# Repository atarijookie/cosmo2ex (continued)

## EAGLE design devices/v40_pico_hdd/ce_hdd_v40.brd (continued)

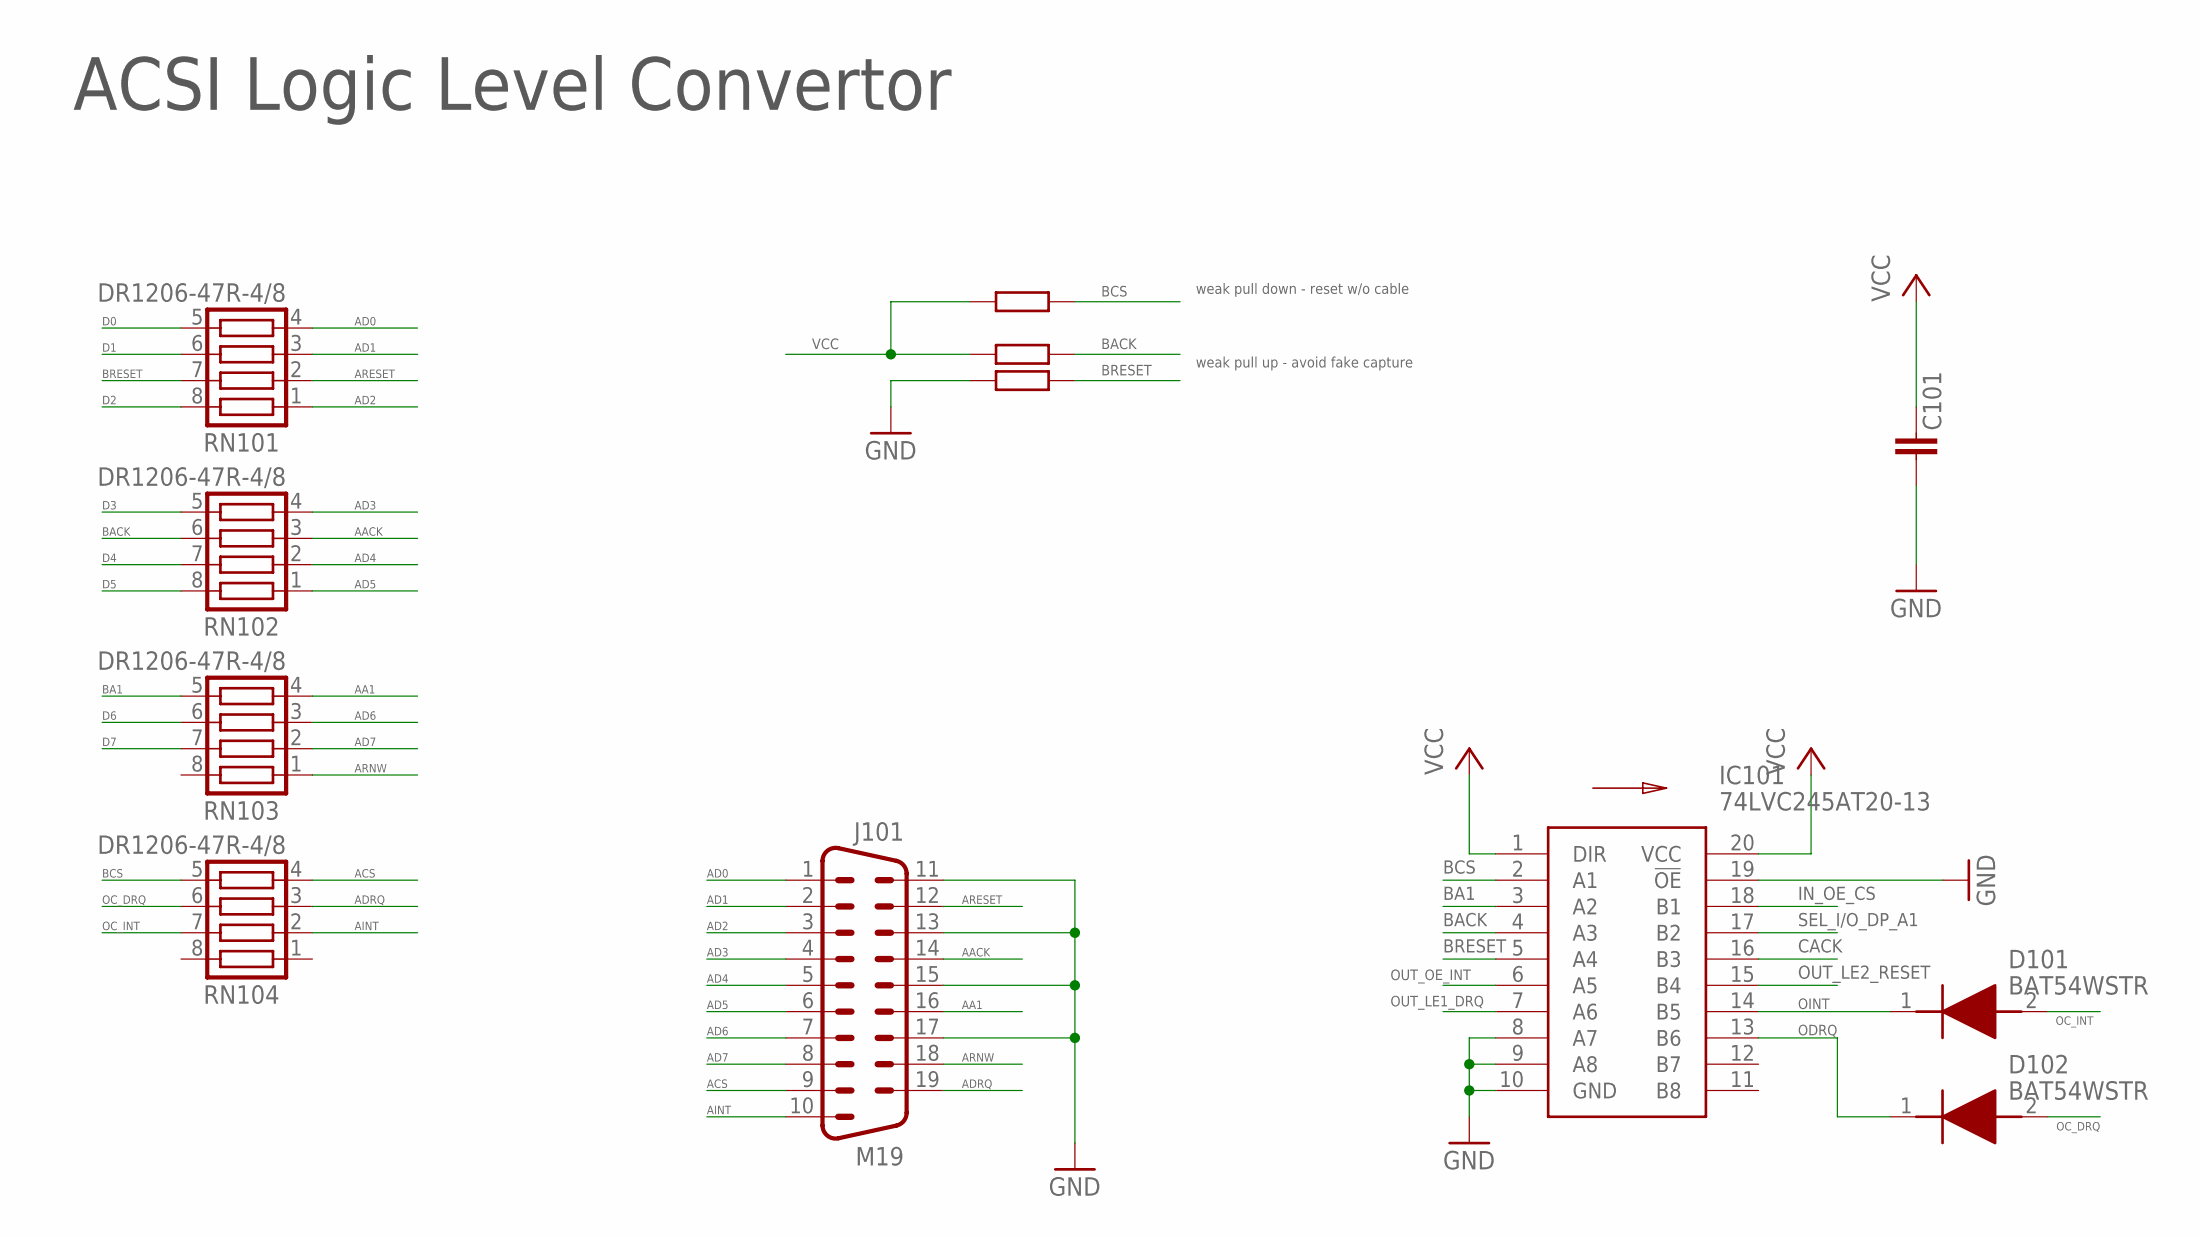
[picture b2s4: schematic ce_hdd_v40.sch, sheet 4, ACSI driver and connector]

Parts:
C101: 1 uF; C0603
D101: BAT54WSTR; SOD2613X100N
D102: BAT54WSTR; SOD2613X100N; MANUFACTURER_PART_NUMBER BAT54WSTR
IC101: 74LVC245AT20-13; SOP65P640X120-20N
J101: M19
R102, R103, R104: 10k; R0603
RN101, RN102, RN103, RN104: DR1206-47R-4/8; CTS742C083

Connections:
AA1: J101.16, RN103.4
AACK: J101.14, RN102.3
ACS: J101.9, RN104.4
AD0: J101.1, RN101.4
AD1: J101.2, RN101.3
AD2: J101.3, RN101.1
AD3: J101.4, RN102.4
AD4: J101.5, RN102.2
AD5: J101.6, RN102.1
AD6: J101.7, RN103.3
AD7: J101.8, RN103.2
ADRQ: J101.19, RN104.3
AINT: J101.10, RN104.2
ARESET: J101.12, RN101.2
ARNW: J101.18, RN103.1
BA1: IC101.3 (A2), RN103.5
BACK: IC101.4 (A3), R103.2, RN102.6
BCS: IC101.2 (A1), R102.2, RN104.5
BRESET: IC101.5 (A4), R104.2, RN101.7
CACK: IC101.16 (B3); also elsewhere on the board
D0: RN101.5; also elsewhere on the board
D1: RN101.6; also elsewhere on the board
D2: RN101.8; also elsewhere on the board
D3: RN102.5; also elsewhere on the board
D4: RN102.7; also elsewhere on the board
D5: RN102.8; also elsewhere on the board
D6: RN103.6; also elsewhere on the board
D7: RN103.7; also elsewhere on the board
GND: C101.2, IC101.8 (A7), IC101.9 (A8), IC101.10 (GND), IC101.19 (!OE), J101.11, J101.13, J101.15, J101.17, R104.1; also elsewhere on the board
IN_OE_CS: IC101.18 (B1); also elsewhere on the board
OC_DRQ: D102.2 (A), RN104.6
OC_INT: D101.2 (A), RN104.7
ODRQ: D102.1 (K), IC101.13 (B6)
OINT: D101.1 (K), IC101.14 (B5)
OUT_LE1_DRQ: IC101.7 (A6); also elsewhere on the board
OUT_LE2_RESET: IC101.15 (B4); also elsewhere on the board
OUT_OE_INT: IC101.6 (A5); also elsewhere on the board
SEL_I/O_DP_A1: IC101.17 (B2); also elsewhere on the board
VCC: C101.1, IC101.1 (DIR), IC101.20 (VCC), R102.1, R103.1; also elsewhere on the board

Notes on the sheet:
ACSI Logic Level Convertor
weak pull down - reset w/o cable
weak pull up - avoid fake capture

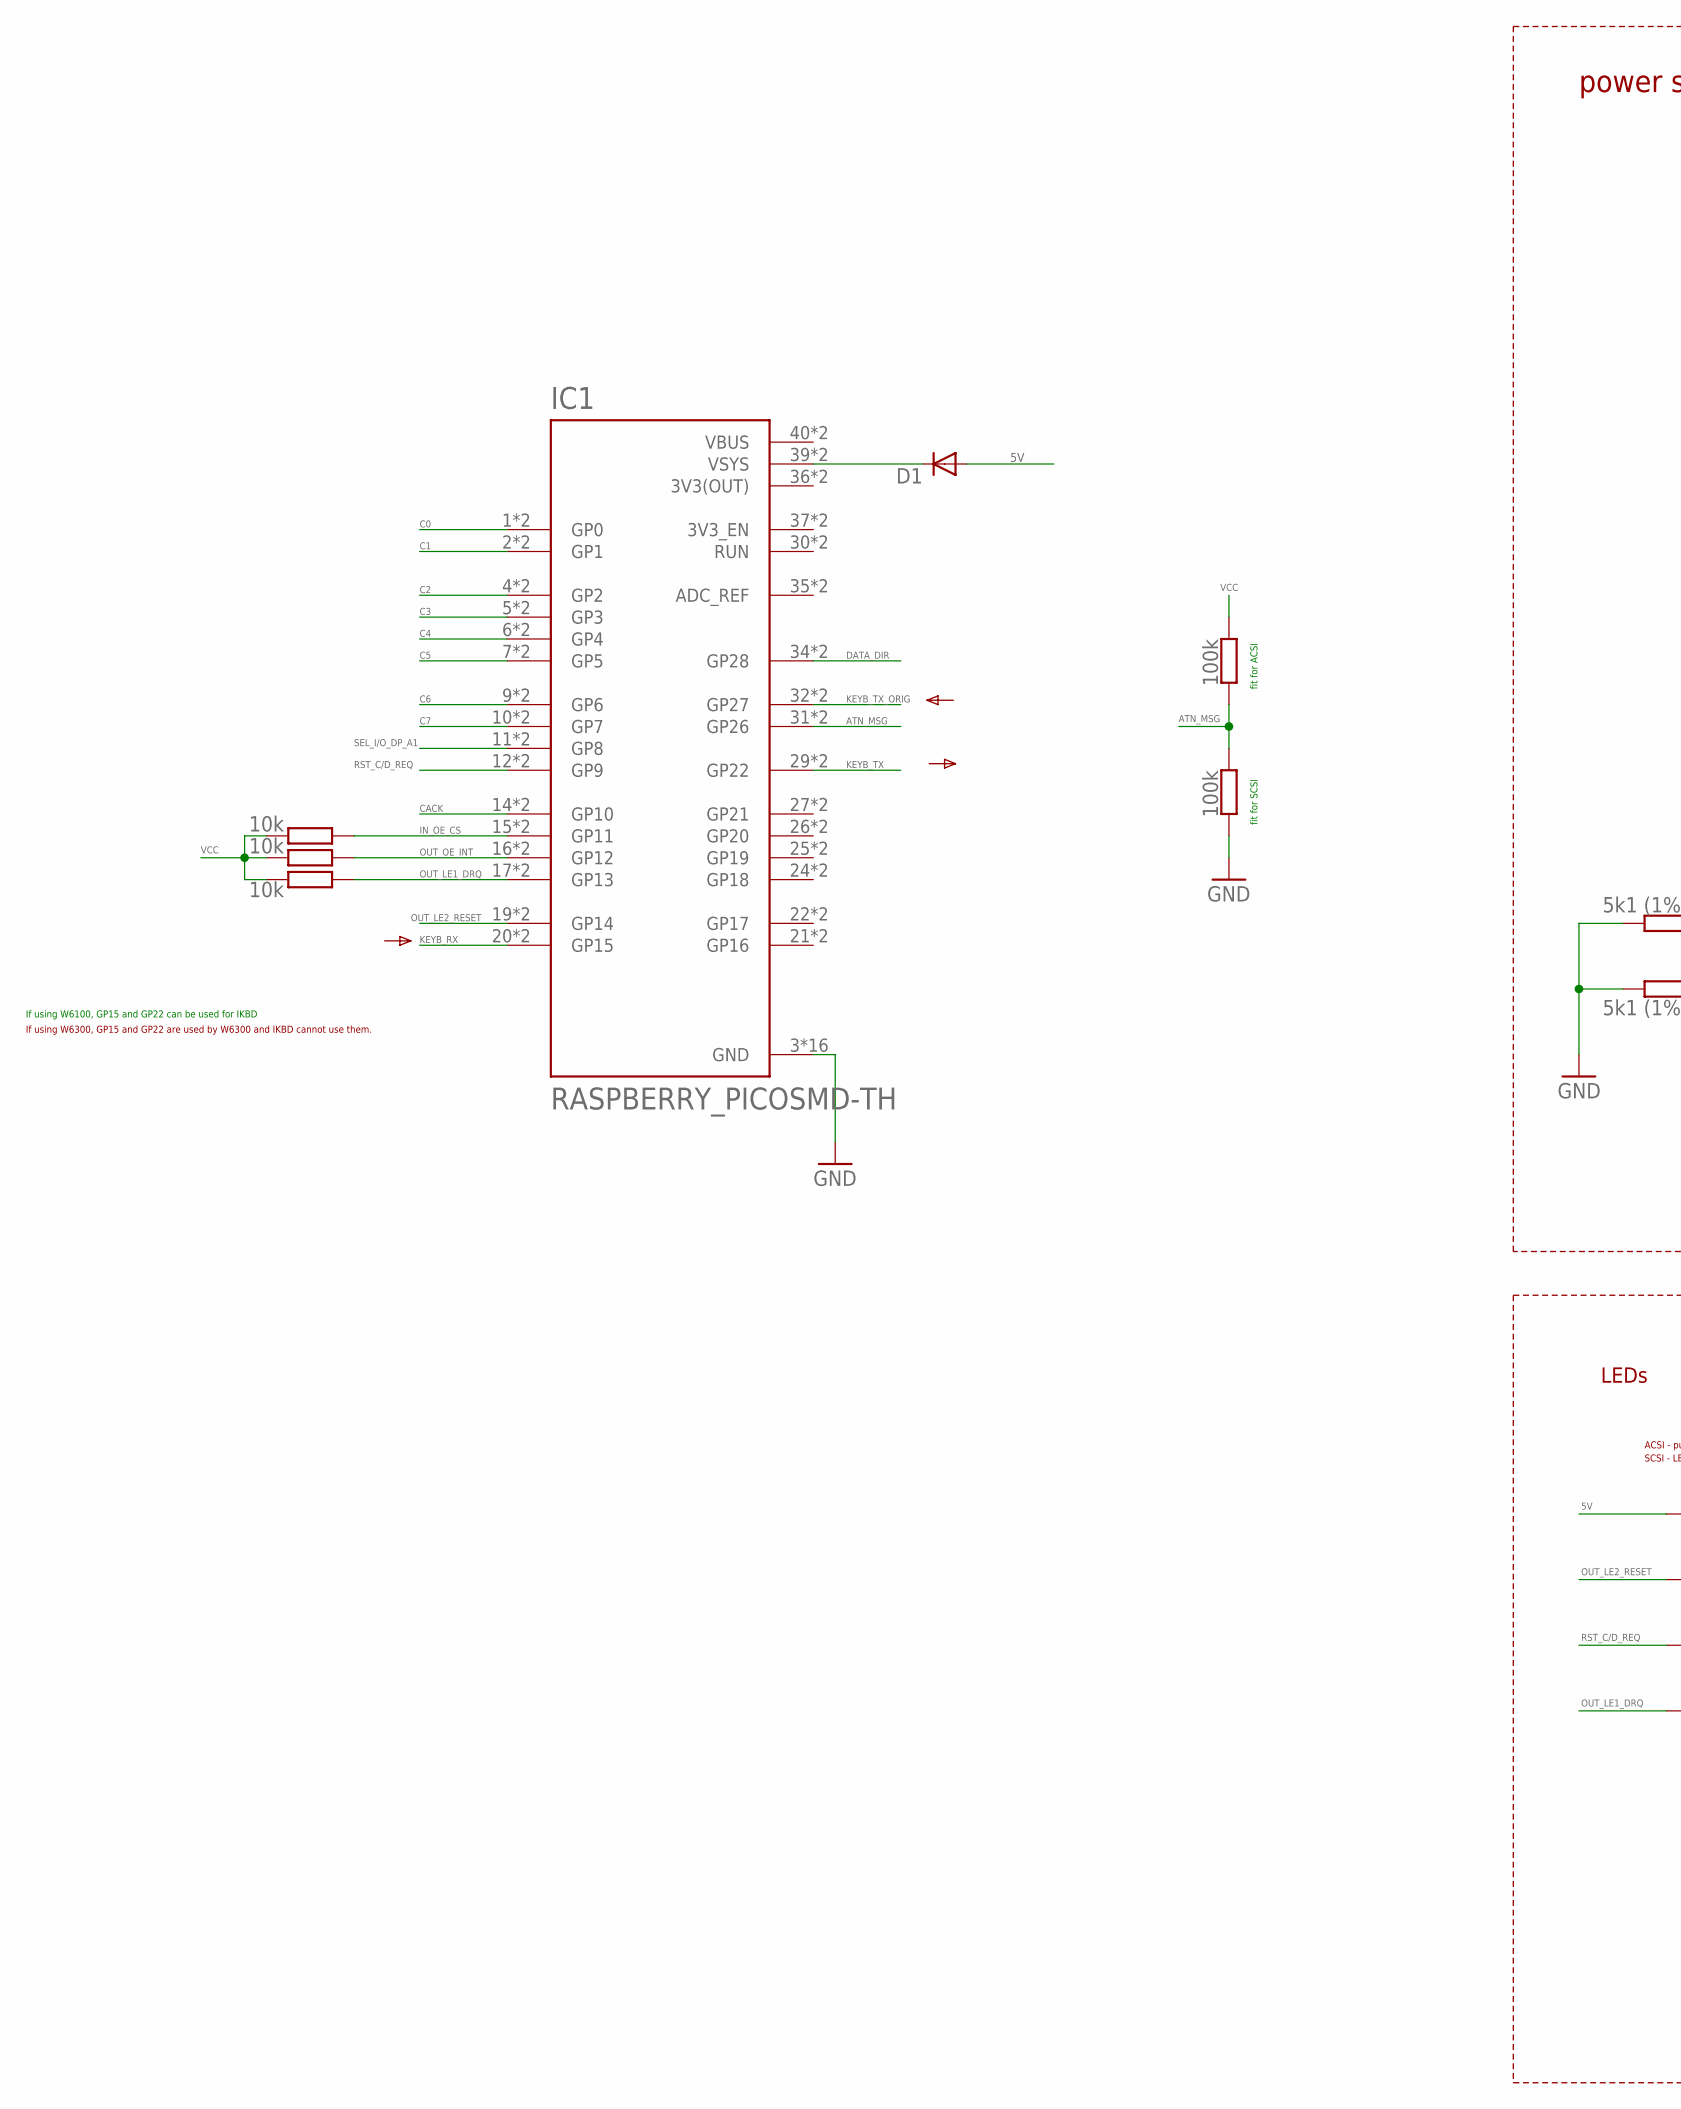
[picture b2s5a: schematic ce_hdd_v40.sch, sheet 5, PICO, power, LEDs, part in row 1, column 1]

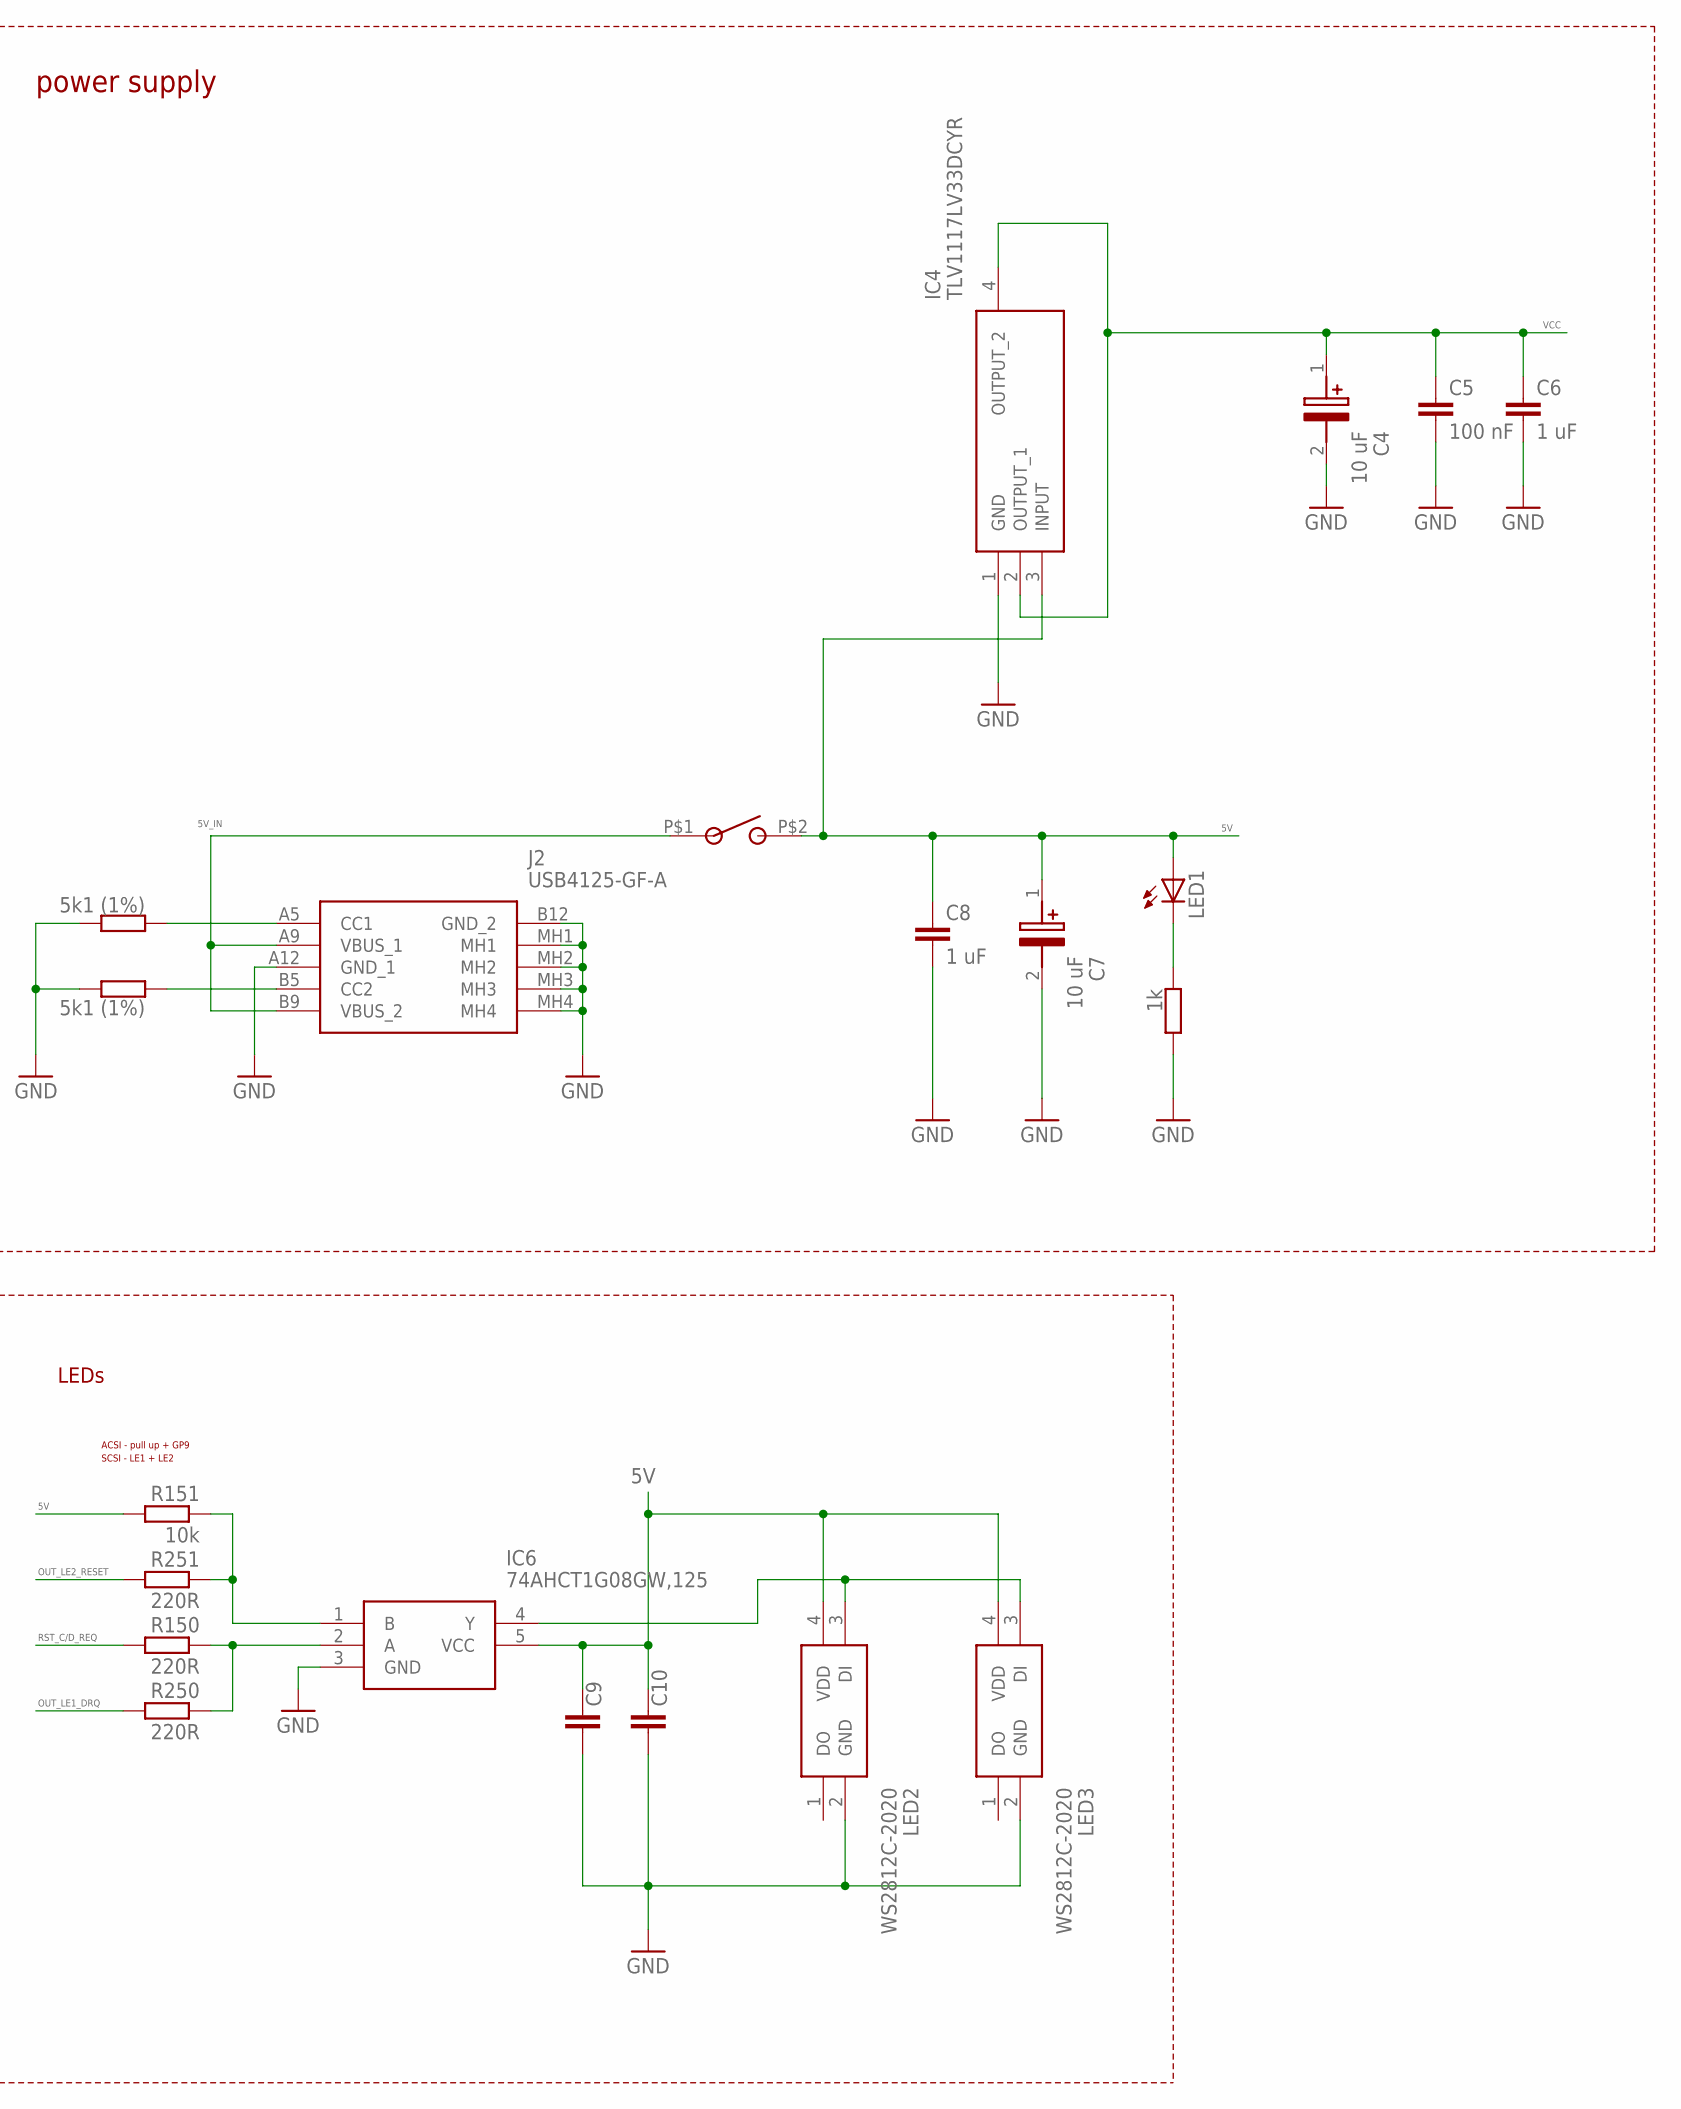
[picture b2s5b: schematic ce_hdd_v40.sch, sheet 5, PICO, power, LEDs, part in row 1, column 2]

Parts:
C4: 10 uF; CAPPM3528X210N; MANUFACTURER_PART_NUMBER 293D106X9016B2TE3
C5, C9, C10: 100 nF; C0603
C6, C8: 1 uF; C0603
C7: 10 uF; CAPPM3528X210N
D1: SK110-DIO; DO214AC
IC1: RASPBERRY_PICOSMD-TH; PICO-PKG
IC4: TLV1117LV33DCYR; SOT230P700X180-4N
IC6: 74AHCT1G08GW,125; SOT65P212X110-5N
J2: USB4125-GF-A; USB4125GFA
LED1: LEDSML0603; SML0603
LED2: WS2812C-2020; WS2812C2020
LED3: WS2812C-2020; WS2812C2020; MANUFACTURER_PART_NUMBER WS2812C-2020
R3, R4: 5k1 (1%); R0603
R5: 1k; R0603
R6, R7, R8, R151: 10k; R0603
R125, R225: 100k; R0603
R150, R250, R251: 220R; R0603
SW1: SMSR-1; SMRS-1

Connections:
3V3(OUT): IC1.36 (3V3(OUT)), IC1.P$36 (3V3(OUT))
5V: C7.1 (+), C8.1, C9.1, C10.1, D1.A, IC4.3 (INPUT), IC6.5 (VCC), LED1.A, LED2.4 (VDD), LED3.4 (VDD), R151.2, SW1.P$2; also elsewhere on the board
5V_IN: J2.A9 (VBUS_1), J2.B9 (VBUS_2), SW1.P$1
ATN_MSG: IC1.31 (GP26), IC1.P$31 (GP26), R125.2, R225.1; also elsewhere on the board
C0: IC1.1 (GP0), IC1.P$1 (GP0); also elsewhere on the board
C1: IC1.2 (GP1), IC1.P$2 (GP1); also elsewhere on the board
C2: IC1.4 (GP2), IC1.P$4 (GP2); also elsewhere on the board
C3: IC1.5 (GP3), IC1.P$5 (GP3); also elsewhere on the board
C4: IC1.6 (GP4), IC1.P$6 (GP4); also elsewhere on the board
C5: IC1.7 (GP5), IC1.P$7 (GP5); also elsewhere on the board
C6: IC1.9 (GP6), IC1.P$9 (GP6); also elsewhere on the board
C7: IC1.10 (GP7), IC1.P$10 (GP7); also elsewhere on the board
CACK: IC1.14 (GP10), IC1.P$14 (GP10); also elsewhere on the board
DATA_DIR: IC1.34 (GP28), IC1.P$34 (GP28); also elsewhere on the board
GND: C4.2 (-), C5.2, C6.2, C7.2 (-), C8.2, C9.2, C10.2, IC1.3 (GND), IC1.8 (GND), IC1.13 (GND), IC1.18 (GND), IC1.23 (GND), IC1.28 (GND), IC1.33 (GND), IC1.38 (GND), IC1.P$3 (GND), IC1.P$8 (GND), IC1.P$13 (GND), IC1.P$18 (GND), IC1.P$23 (GND), IC1.P$28 (GND), IC1.P$33 (GND), IC1.P$38 (GND), IC4.1 (GND), IC6.3 (GND), J2.A12 (GND_1), J2.B12 (GND_2), J2.MH1, J2.MH2, J2.MH3, J2.MH4, LED2.2 (GND), LED3.2 (GND), R3.2, R4.2, R5.2, R225.2; also elsewhere on the board
IN_OE_CS: IC1.15 (GP11), IC1.P$15 (GP11), R6.2; also elsewhere on the board
KEYB_RX: IC1.20 (GP15), IC1.P$20 (GP15); also elsewhere on the board
KEYB_TX: IC1.29 (GP22), IC1.P$29 (GP22); also elsewhere on the board
KEYB_TX_ORIG: IC1.32 (GP27), IC1.P$32 (GP27); also elsewhere on the board
unnamed: J2.B5 (CC2), R4.1
unnamed: J2.A5 (CC1), R3.1
unnamed: IC6.2 (A), R150.1, R250.1
unnamed: IC6.1 (B), R151.1, R251.1
unnamed: LED1.C, R5.1
unnamed: IC6.4 (Y), LED2.3 (DI), LED3.3 (DI)
unnamed: D1.C, IC1.39 (VSYS), IC1.P$39 (VSYS)
OUT_LE1_DRQ: IC1.17 (GP13), IC1.P$17 (GP13), R8.2, R250.2; also elsewhere on the board
OUT_LE2_RESET: IC1.19 (GP14), IC1.P$19 (GP14), R251.2; also elsewhere on the board
OUT_OE_INT: IC1.16 (GP12), IC1.P$16 (GP12), R7.2; also elsewhere on the board
RST_C/D_REQ: IC1.12 (GP9), IC1.P$12 (GP9), R150.2; also elsewhere on the board
SEL_I/O_DP_A1: IC1.11 (GP8), IC1.P$11 (GP8); also elsewhere on the board
VBUS: IC1.40 (VBUS), IC1.P$40 (VBUS)
VCC: C4.1 (+), C5.1, C6.1, IC4.2 (OUTPUT_1), IC4.4 (OUTPUT_2), R6.1, R7.1, R8.1, R125.1; also elsewhere on the board

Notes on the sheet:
power supply
If using W6100, GP15 and GP22 can be used for IKBD
If using W6300, GP15 and GP22 are used by W6300 and IKBD cannot use them.
fit for ACSI
fit for SCSI
LEDs
ACSI - pull up + GP9
SCSI - LE1 + LE2

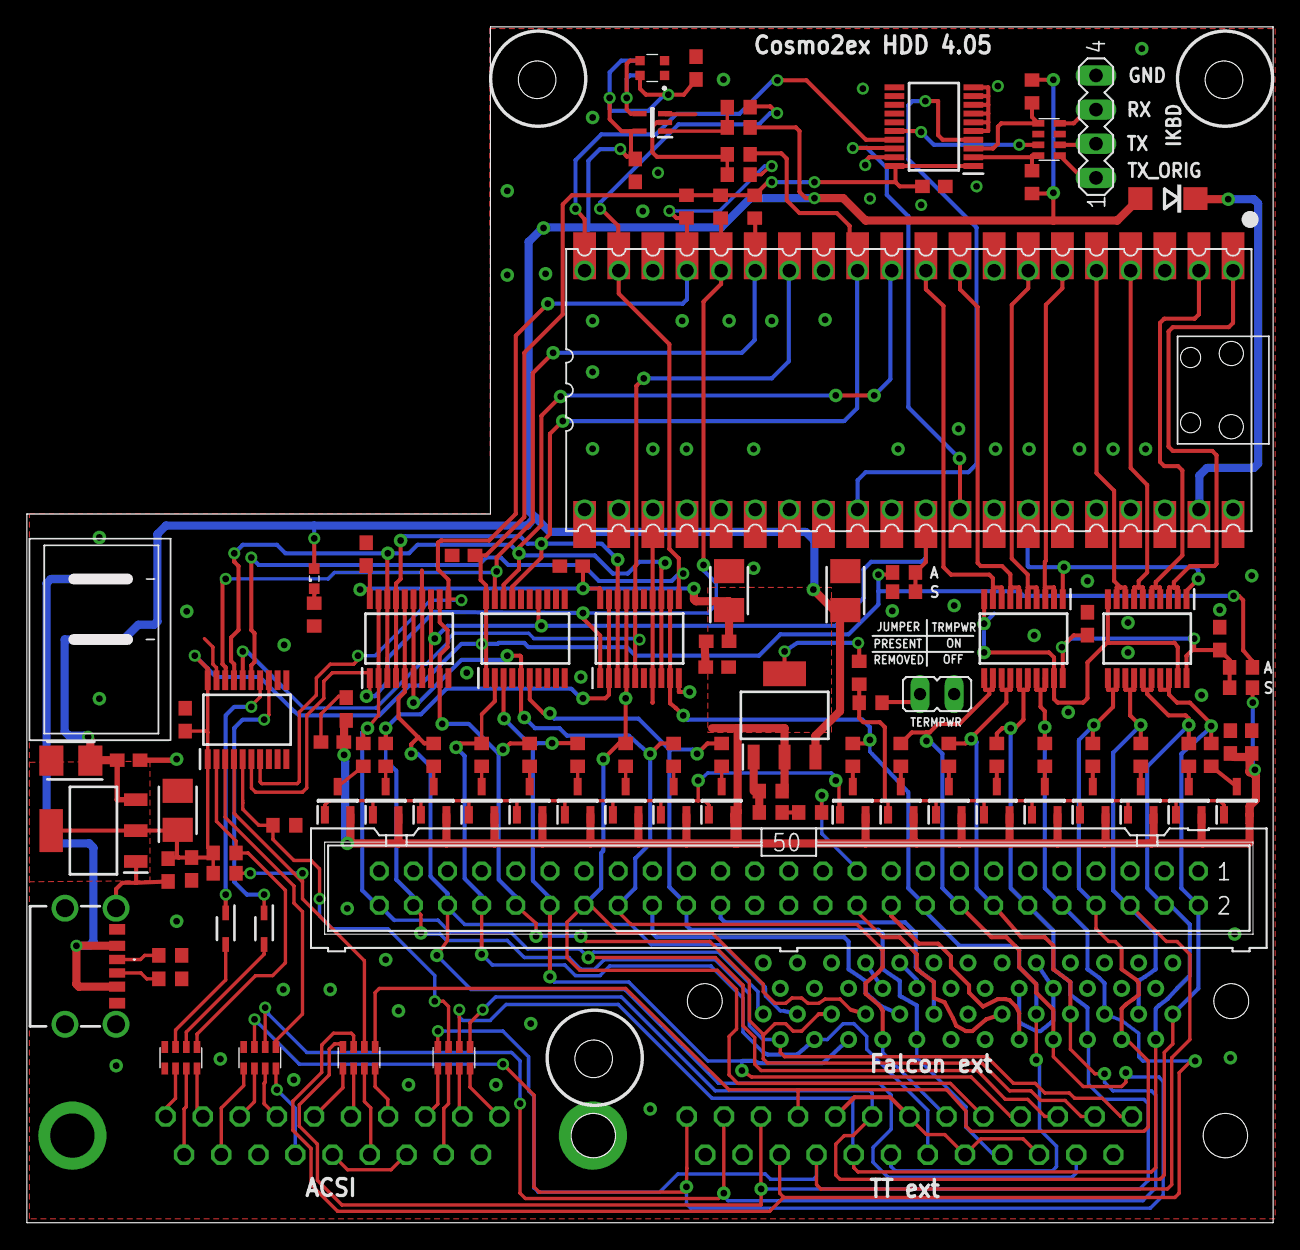
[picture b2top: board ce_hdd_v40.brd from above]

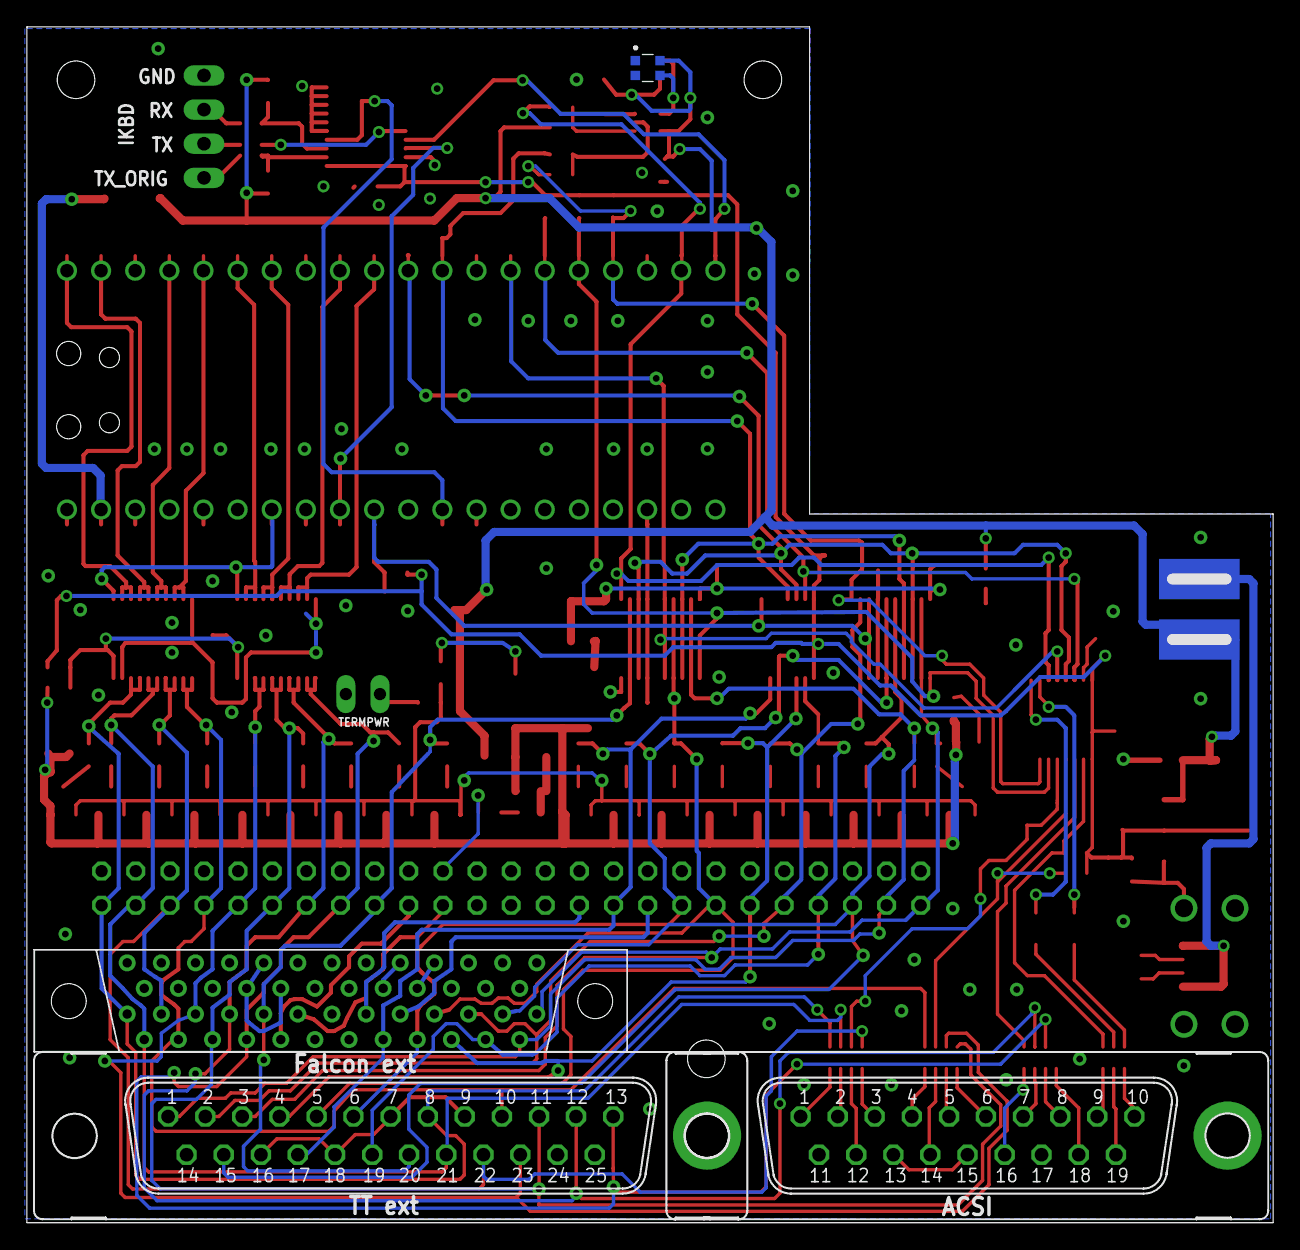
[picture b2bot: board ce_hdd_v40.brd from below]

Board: 2 copper layers, 92.8 x 89.0 mm, 112 parts (4 on the bottom side), 104 nets.

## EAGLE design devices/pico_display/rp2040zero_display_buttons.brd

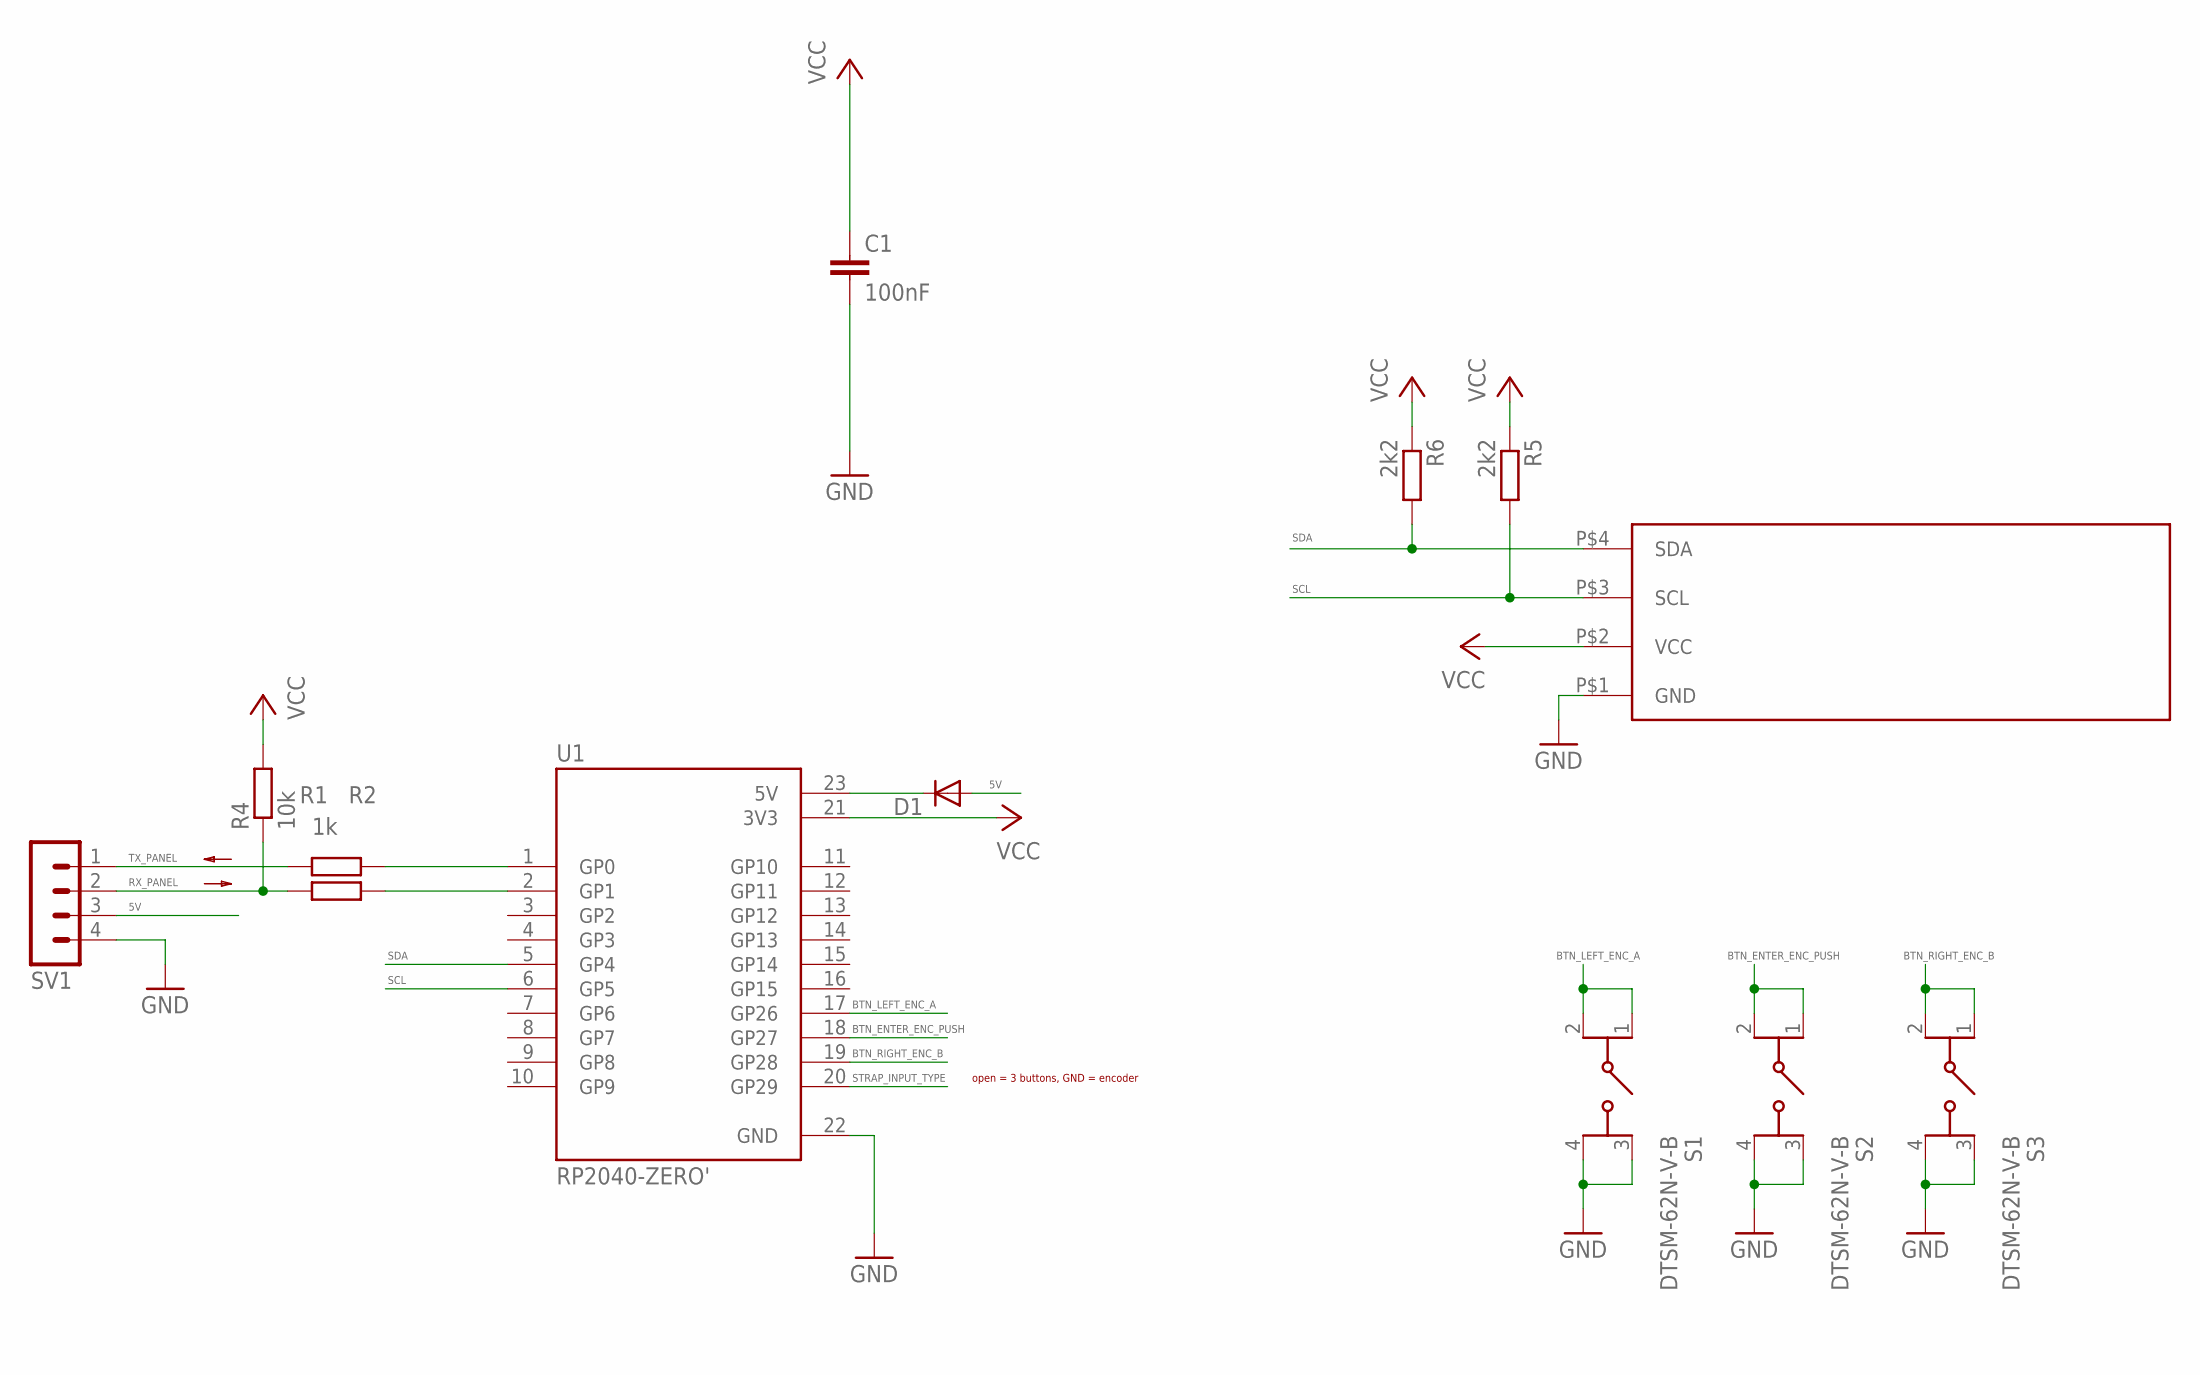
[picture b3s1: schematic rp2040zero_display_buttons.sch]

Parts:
C1: 100nF; C0603
D1: SK110-DIO; DO214AC
R1, R2: 1k; R0603
R4: 10k; R0603
R5, R6: 2k2; R0603
S1, S2, S3: DTSM-62N-V-B; DTSM62NVB
SV1: MA04-1
U1: RP2040-ZERO'; MODULE_RP2040-ZERO
U$1: OLED; SIP

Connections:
5V: D1.A, SV1.3
BTN_ENTER_ENC_PUSH: S2.1 (COM_1), S2.2 (COM_2), U1.18 (GP27)
BTN_LEFT_ENC_A: S1.1 (COM_1), S1.2 (COM_2), U1.17 (GP26)
BTN_RIGHT_ENC_B: S3.1 (COM_1), S3.2 (COM_2), U1.19 (GP28)
GND: C1.2, S1.3 (NO_1), S1.4 (NO_2), S2.3 (NO_1), S2.4 (NO_2), S3.3 (NO_1), S3.4 (NO_2), SV1.4, U1.22 (GND), U$1.P$1 (GND)
unnamed: R1.2, U1.1 (GP0)
unnamed: R2.2, U1.2 (GP1)
unnamed: D1.C, U1.23 (5V)
RX_PANEL: R2.1, R4.1, SV1.2
SCL: R5.2, U1.6 (GP5), U$1.P$3 (SCL)
SDA: R6.2, U1.5 (GP4), U$1.P$4 (SDA)
STRAP_INPUT_TYPE: U1.20 (GP29)
TX_PANEL: R1.1, SV1.1
VCC: C1.1, R4.2, R5.1, R6.1, U1.21 (3V3), U$1.P$2 (VCC)

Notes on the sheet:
open = 3 buttons, GND = encoder

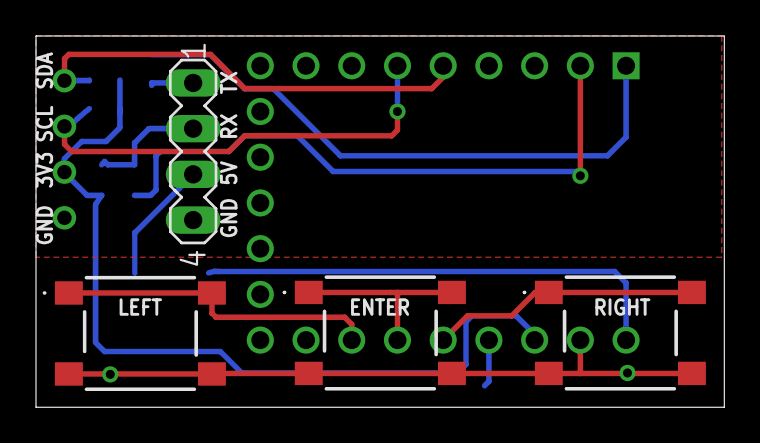
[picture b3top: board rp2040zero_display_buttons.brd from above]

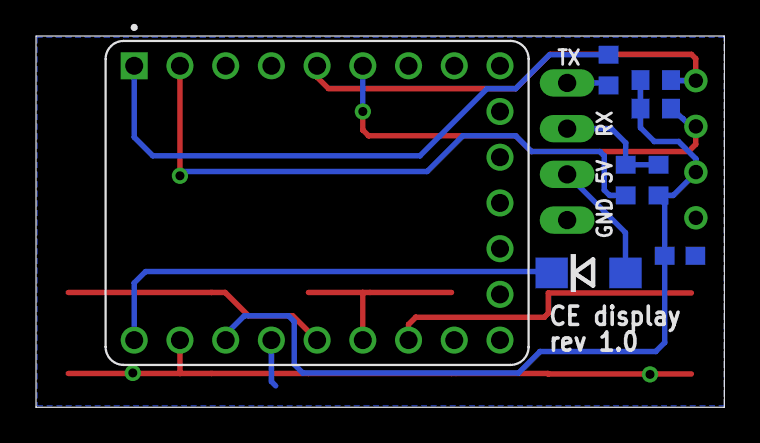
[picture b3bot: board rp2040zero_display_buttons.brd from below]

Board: 2 copper layers, 38.2 x 20.6 mm, 13 parts (8 on the bottom side), 13 nets.

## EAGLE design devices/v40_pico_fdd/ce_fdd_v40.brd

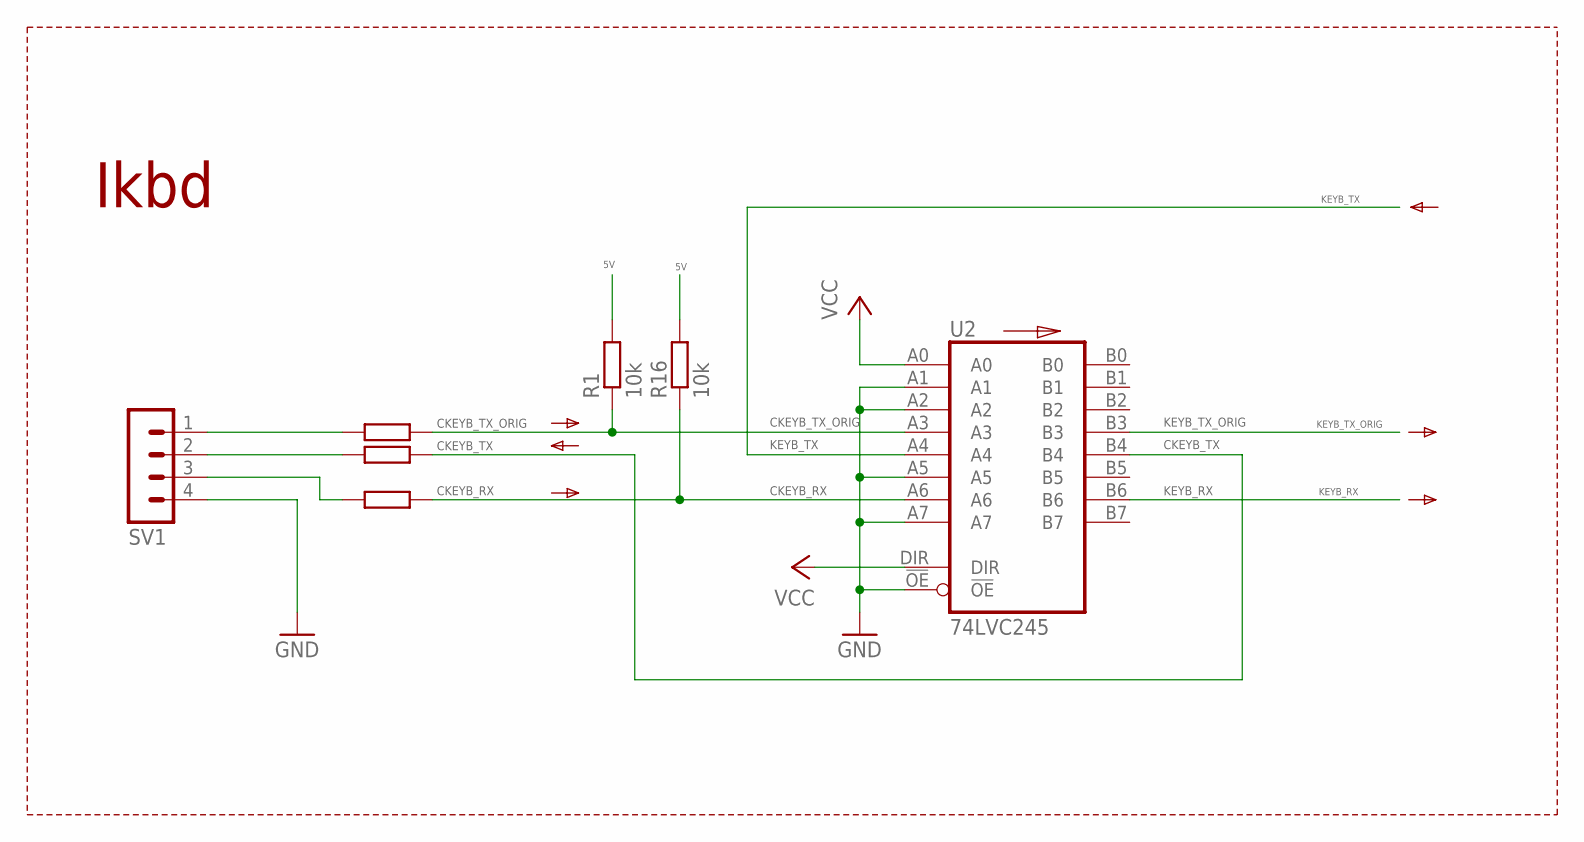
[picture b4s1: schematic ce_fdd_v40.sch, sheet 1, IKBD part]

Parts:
R1, R16: 10k; R0603
R25, R33, R34: 47R; R0603
SV1: MA04-1
U2: 74LVC245; 74LVC245_TSSOP20

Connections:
5V: R1.2, R16.2; also elsewhere on the board
CKEYB_RX: R16.1, R34.1, U2.A6
CKEYB_TX: R33.1, U2.B4
CKEYB_TX_ORIG: R1.1, R25.1, U2.A3
GND: SV1.4, U2.!OE, U2.A1, U2.A2, U2.A5, U2.A7, U2.GND; also elsewhere on the board
KEYB_RX: U2.B6; also elsewhere on the board
KEYB_TX: U2.A4; also elsewhere on the board
KEYB_TX_ORIG: U2.B3; also elsewhere on the board
unnamed: R33.2, SV1.2
VCC: U2.A0, U2.DIR, U2.VCC; also elsewhere on the board
ZKEYB_RX: R34.2, SV1.3
ZKEYB_TX_ORIG: R25.2, SV1.1

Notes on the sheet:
Ikbd
